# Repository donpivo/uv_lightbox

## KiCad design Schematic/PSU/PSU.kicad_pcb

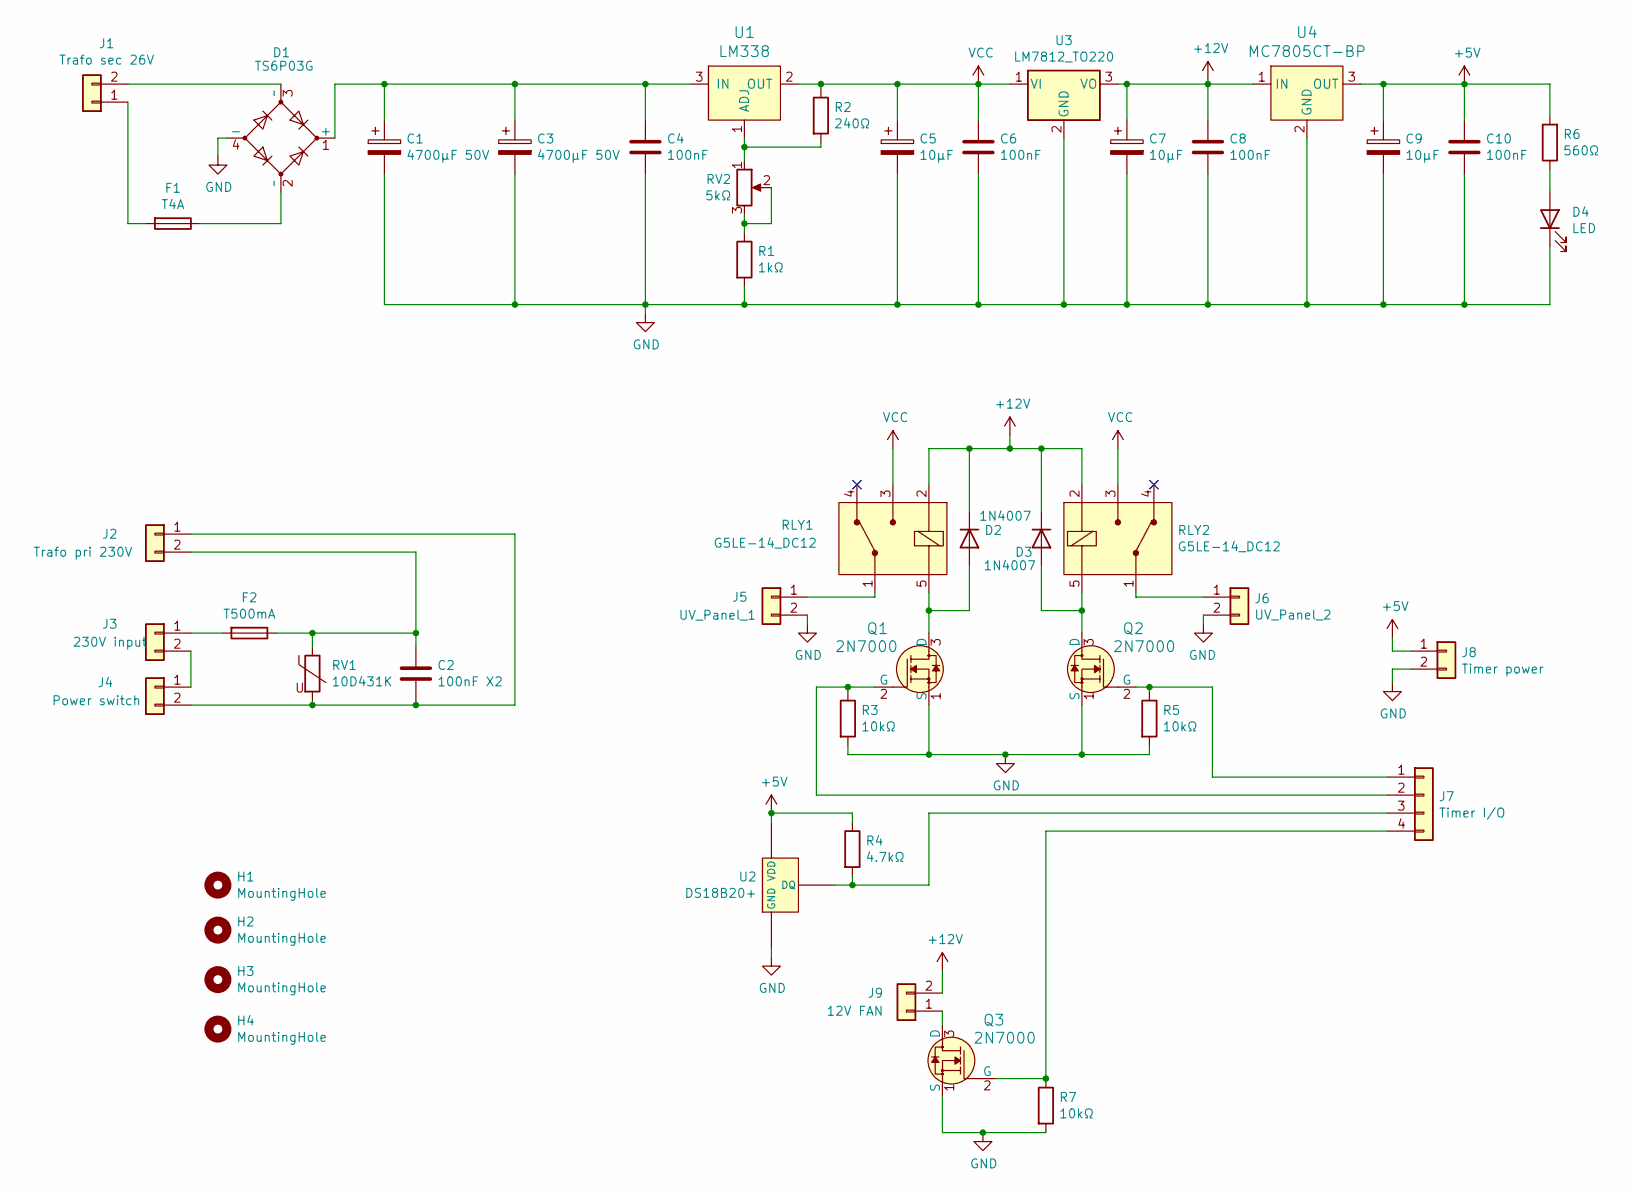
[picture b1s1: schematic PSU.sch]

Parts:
C1, C3: 4700µF 50V; CP_Radial_D22.0mm_P10.00mm_SnapIn
C2: 100nF X2; C_Rect_L18.0mm_W6.0mm_P15.00mm_FKS3_FKP3
C4, C6, C8, C10: 100nF; C_Rect_L7.2mm_W2.5mm_P5.00mm_FKS2_FKP2_MKS2_MKP2
C5, C7, C9: 10µF; CP_Radial_D5.0mm_P2.00mm
D1: TS6P03G; Generic_rectifier
D2, D3: 1N4007; D_DO-41_SOD81_P10.16mm_Horizontal
D4: LED; LED_D3.0mm
F1: T4A; Fuseholder_Cylinder-5x20mm_Closed
F2: T500mA; Fuseholder_Cylinder-5x20mm_Closed
H1, H2, H3, H4: MountingHole; MountingHole_3.2mm_M3
J1: Trafo sec 26V; TerminalBlock_LCSC_P5.08mm
J2: Trafo pri 230V; TerminalBlock_LCSC_P5.08mm
J3: 230V input; TerminalBlock_LCSC_P5.08mm
J4: Power switch; TerminalBlock_LCSC_P5.08mm
J5: UV_Panel_1; TerminalBlock_LCSC_P5.08mm
J6: UV_Panel_2; TerminalBlock_LCSC_P5.08mm
J7: Timer I/O; KF2510-4P
J8: Timer power; KF2510-2P
J9: 12V FAN; KF2510-2P
Q1, Q2, Q3: 2N7000; TO-92-3; MPN 2N7000; Digi-Key_PN 2N7000FS-ND
R1: 1kΩ; R_Axial_DIN0207_L6.3mm_D2.5mm_P7.62mm_Horizontal
R2: 240Ω; R_Axial_DIN0207_L6.3mm_D2.5mm_P7.62mm_Horizontal
R3, R5, R7: 10kΩ; R_Axial_DIN0207_L6.3mm_D2.5mm_P7.62mm_Horizontal
R4: 4.7kΩ; R_Axial_DIN0207_L6.3mm_D2.5mm_P7.62mm_Horizontal
R6: 560Ω; R_Axial_DIN0207_L6.3mm_D2.5mm_P7.62mm_Horizontal
RLY1, RLY2: G5LE-14_DC12; Relay_THT_G5LE-14; MPN G5LE-14 DC12; Digi-Key_PN Z1012-ND
RV1: 10D431K; RV_Disc_D12mm_W4.5mm_P7.5mm
RV2: 5kΩ; Potentiometer_Bourns_3296W_Vertical
U1: LM338; TO-220-3; MPN LM317T; Digi-Key_PN 497-1575-5-ND
U2: DS18B20+; TO127P482X368X883-3
U3: LM7812_TO220; TO-220-3
U4: MC7805CT-BP; TO-220-3; MPN MC7805CT-BP; Digi-Key_PN MC7805CT-BPMS-ND

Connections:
+5V: C9.1, C10.1, J8.1, R4.1, R6.2, U2.3 (VDD), U4.3 (OUT)
+12V: C7.1, C8.1, D2.1 (K), D3.1 (K), J9.2, RLY1.2 (COIL), RLY2.2 (COIL), U3.3 (VO), U4.1 (IN)
GND: C1.2, C3.2, C4.2, C5.2, C6.2, C7.2, C8.2, C9.2, C10.2, D1.4 (-), D4.1 (K), J5.2, J6.2, J8.2, Q1.1 (S), Q2.1 (S), Q3.1 (S), R1.2, R3.2, R5.2, R7.2, U2.1 (GND), U3.2 (GND), U4.2 (GND)
unnamed: C1.1, C3.1, C4.1, D1.1 (+), U1.3 (IN)
unnamed: C2.1, F2.1, J2.2, RV1.1
unnamed: C2.2, J2.1, J4.2, RV1.2
unnamed: D1.2 (~~), F1.1
unnamed: D1.3 (~~), J1.2
unnamed: D2.2 (A), Q1.3 (D), RLY1.5 (COIL)
unnamed: D3.2 (A), Q2.3 (D), RLY2.5 (COIL)
unnamed: D4.2 (A), R6.1
unnamed: F1.2, J1.1
unnamed: F2.2, J3.1
unnamed: J3.2, J4.1
unnamed: J5.1, RLY1.1 (COM)
unnamed: J6.1, RLY2.1 (COM)
unnamed: J7.1, Q2.2 (G), R5.1
unnamed: J7.2, Q1.2 (G), R3.1
unnamed: J7.3, R4.2, U2.2 (DQ)
unnamed: J7.4, Q3.2 (G), R7.1
unnamed: J9.1, Q3.3 (D)
unnamed: R1.1, RV2.2, RV2.3
unnamed: R2.2, RV2.1, U1.1 (ADJ)
VCC: C5.1, C6.1, R2.1, RLY1.3 (NO), RLY2.3 (NO), U1.2 (OUT), U3.1 (VI)

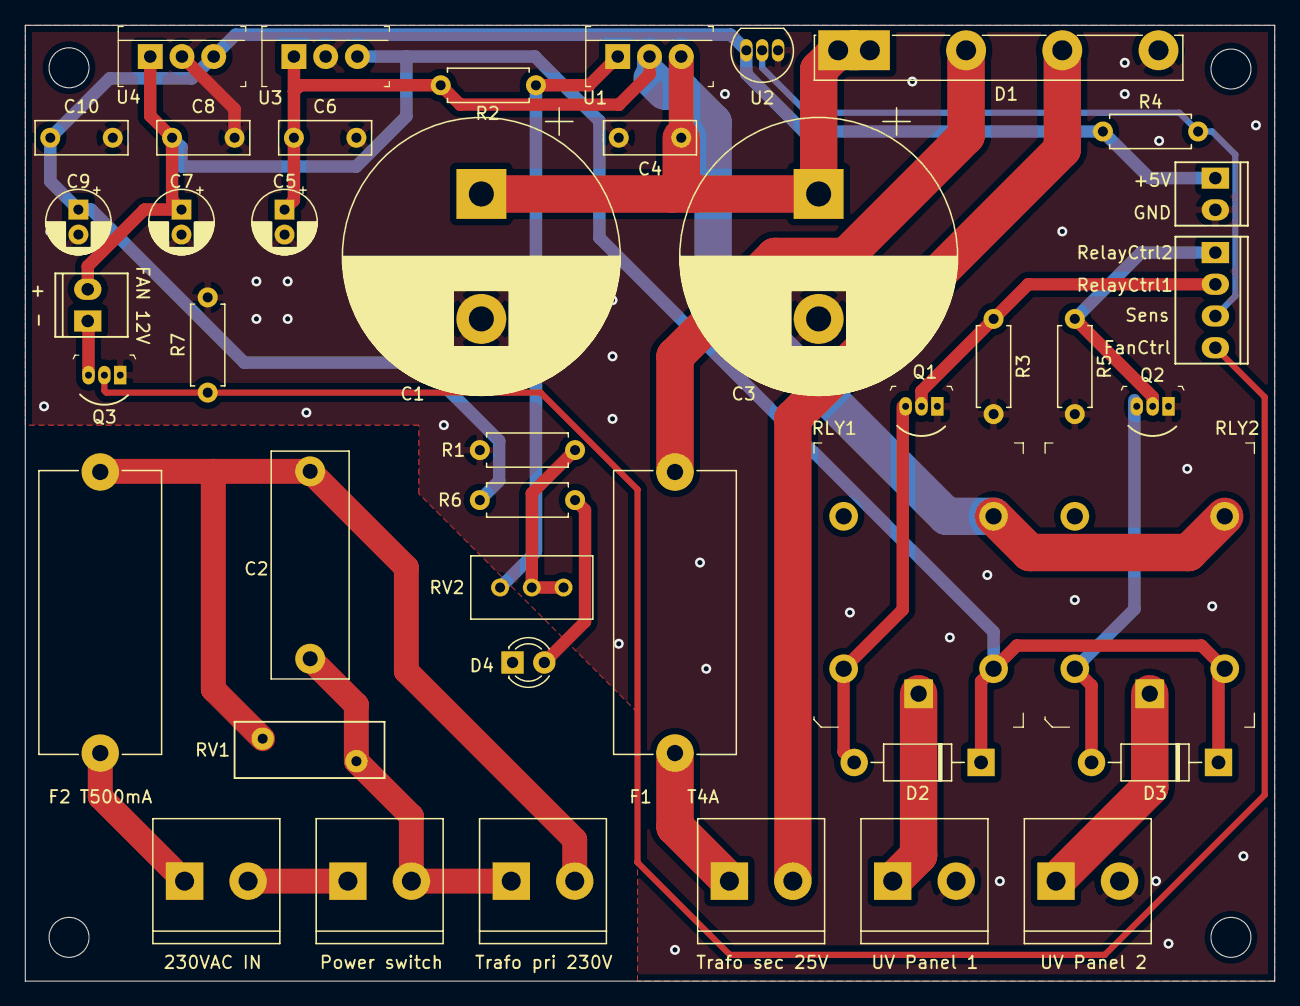
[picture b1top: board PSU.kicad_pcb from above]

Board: 2 copper layers, 100.0 x 76.5 mm, 47 parts (0 on the bottom side), 24 nets.

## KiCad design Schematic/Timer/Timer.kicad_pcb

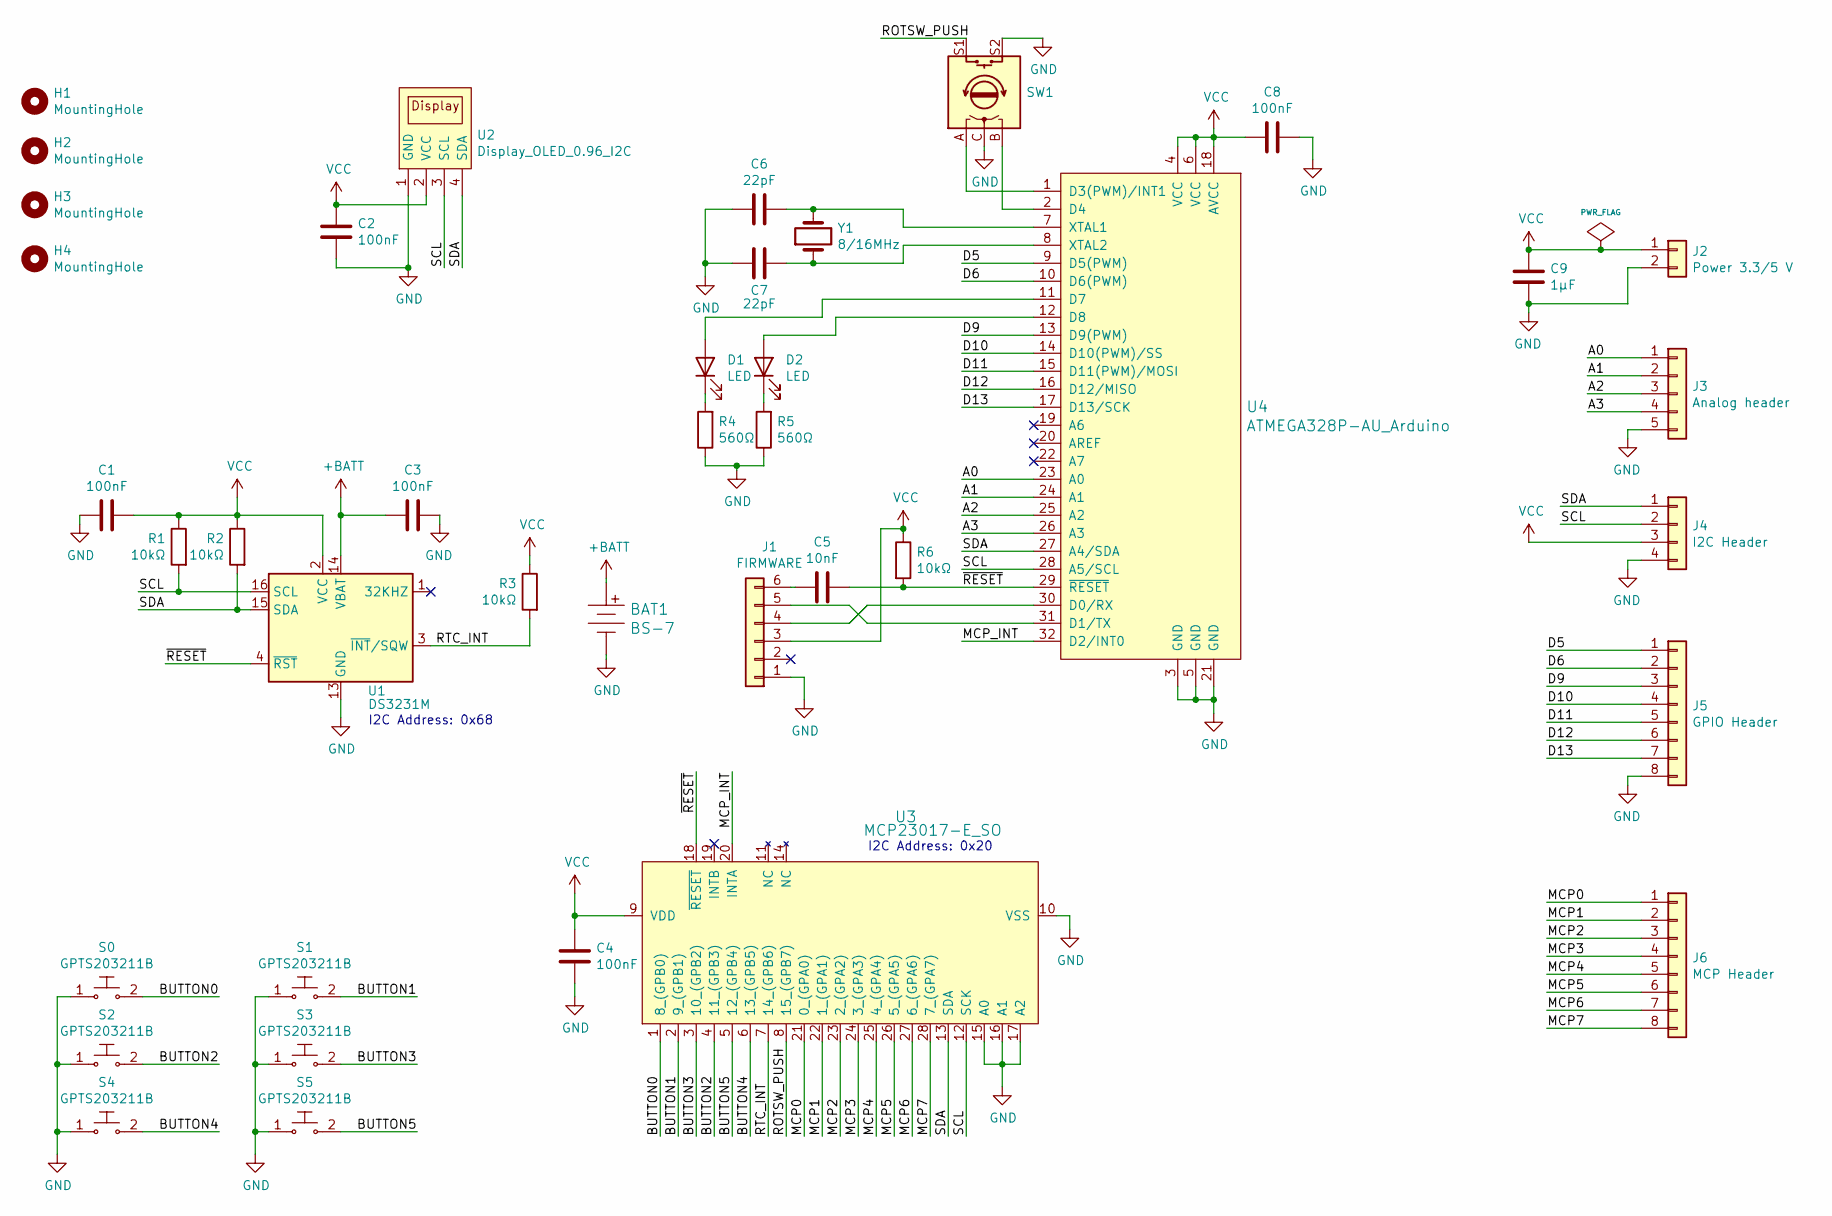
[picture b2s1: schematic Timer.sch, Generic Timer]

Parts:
BAT1: BS-7; Battery_Holder_Coin_2032_BS-7; MPN BS-7; Digi-Key_PN BS-7-ND
C1, C2, C3, C4, C8: 100nF; C_0805_2012Metric_Pad1.15x1.40mm_HandSolder
C5: 10nF; C_0805_2012Metric_Pad1.15x1.40mm_HandSolder
C6, C7: 22pF; C_0805_2012Metric_Pad1.15x1.40mm_HandSolder
C9: 1µF; C_0805_2012Metric_Pad1.15x1.40mm_HandSolder
D1, D2: LED; LED_0805_2012Metric_Pad1.15x1.40mm_HandSolder
H1, H2, H3, H4: MountingHole; MountingHole_3.2mm_M3
J1: FIRMWARE; PinHeader_1x06_P2.54mm_Vertical
J2: Power 3.3/5 V; KF2510-2P
J3: Analog header; KF2510-5P
J4: I2C Header; KF2510-4P
J5: GPIO Header; KF2510-8P
J6: MCP Header; KF2510-8P
R1, R2, R3, R6: 10kΩ; R_0805_2012Metric_Pad1.15x1.40mm_HandSolder
R4, R5: 560Ω; R_0805_2012Metric_Pad1.15x1.40mm_HandSolder
S0, S1, S2, S3, S4, S5: GPTS203211B; SW_PUSH_6mm_H7.3mm; MPN GPTS203211B; Digi-Key_PN CW181-ND
SW1: Rotary_Encoder_Switch; RotaryEncoder_Alps_EC11E-Switch_Vertical_H20mm
U1: DS3231M; SOIC-16W_7.5x10.3mm_P1.27mm
U2: Display_OLED_0.96_I2C; Display_OLED_0.96in_I2C
U3: MCP23017-E_SO; SOIC-28_W7.5mm
U4: ATMEGA328P-AU_Arduino; TQFP-32_7x7mm
Y1: 8/16MHz; Crystal_SMD_HC49-SD

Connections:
+BATT: BAT1.Pos, C3.1, U1.14 (VBAT)
/A0: J3.1, U4.23 (A0)
/A1: J3.2, U4.24 (A1)
/A2: J3.3, U4.25 (A2)
/A3: J3.4, U4.26 (A3)
/BUTTON0: S0.2, U3.1 (8_(GPB0))
/BUTTON1: S1.2, U3.2 (9_(GPB1))
/BUTTON2: S2.2, U3.4 (11_(GPB3))
/BUTTON3: S3.2, U3.3 (10_(GPB2))
/BUTTON4: S4.2, U3.6 (13_(GPB5))
/BUTTON5: S5.2, U3.5 (12_(GPB4))
/D5: J5.1, U4.9 (D5(PWM))
/D6: J5.2, U4.10 (D6(PWM))
/D9: J5.3, U4.13 (D9(PWM))
/D10: J5.4, U4.14 (D10(PWM)/SS)
/D11: J5.5, U4.15 (D11(PWM)/MOSI)
/D12: J5.6, U4.16 (D12/MISO)
/D13: J5.7, U4.17 (D13/SCK)
/MCP0: J6.1, U3.21 (0_(GPA0))
/MCP1: J6.2, U3.22 (1_(GPA1))
/MCP2: J6.3, U3.23 (2_(GPA2))
/MCP3: J6.4, U3.24 (3_(GPA3))
/MCP4: J6.5, U3.25 (4_(GPA4))
/MCP5: J6.6, U3.26 (5_(GPA5))
/MCP6: J6.7, U3.27 (6_(GPA6))
/MCP7: J6.8, U3.28 (7_(GPA7))
/MCP_INT: U3.20 (INTA), U4.32 (D2/INT0)
/ROTSW_PUSH: SW1.S1, U3.8 (15_(GPB7))
/RTC_INT: R3.2, U1.3 (~INT~/SQW), U3.7 (14_(GPB6))
/SCL: J4.2, R1.2, U1.16 (SCL), U2.3 (SCL), U3.12 (SCK), U4.28 (A5/SCL)
/SDA: J4.1, R2.2, U1.15 (SDA), U2.4 (SDA), U3.13 (SDA), U4.27 (A4/SDA)
/~RESET: C5.2, R6.2, U1.4 (~RST), U3.18 (~RESET), U4.29 (~RESET~)
GND: BAT1.Neg, C1.2, C2.1, C3.2, C4.1, C6.1, C7.1, C8.1, C9.1, J1.1, J2.2, J3.5, J4.4, J5.8, R4.1, R5.1, S0.1, S1.1, S2.1, S3.1, S4.1, S5.1, SW1.C, SW1.S2, U1.5 (GND), U1.6 (GND), U1.7 (GND), U1.8 (GND), U1.9 (GND), U1.10 (GND), U1.11 (GND), U1.12 (GND), U1.13 (GND), U2.1 (GND), U3.10 (VSS), U3.15 (A0), U3.16 (A1), U3.17 (A2), U4.3 (GND), U4.5 (GND), U4.21 (GND)
unnamed: C5.1, J1.6
unnamed: C6.2, U4.7 (XTAL1), Y1.2
unnamed: C7.2, U4.8 (XTAL2), Y1.1
unnamed: D1.1 (K), R4.2
unnamed: D1.2 (A), U4.11 (D7)
unnamed: D2.1 (K), R5.2
unnamed: D2.2 (A), U4.12 (D8)
unnamed: J1.4, U4.30 (D0/RX)
unnamed: J1.5, U4.31 (D1/TX)
unnamed: SW1.A, U4.1 (D3(PWM)/INT1)
unnamed: SW1.B, U4.2 (D4)
VCC: C1.1, C2.2, C4.2, C8.2, C9.2, J1.3, J2.1, J4.3, R1.1, R2.1, R3.1, R6.1, U1.2 (VCC), U2.2 (VCC), U3.9 (VDD), U4.4 (VCC), U4.6 (VCC), U4.18 (AVCC)

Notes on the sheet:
I2C Address: 0x68
I2C Address: 0x20

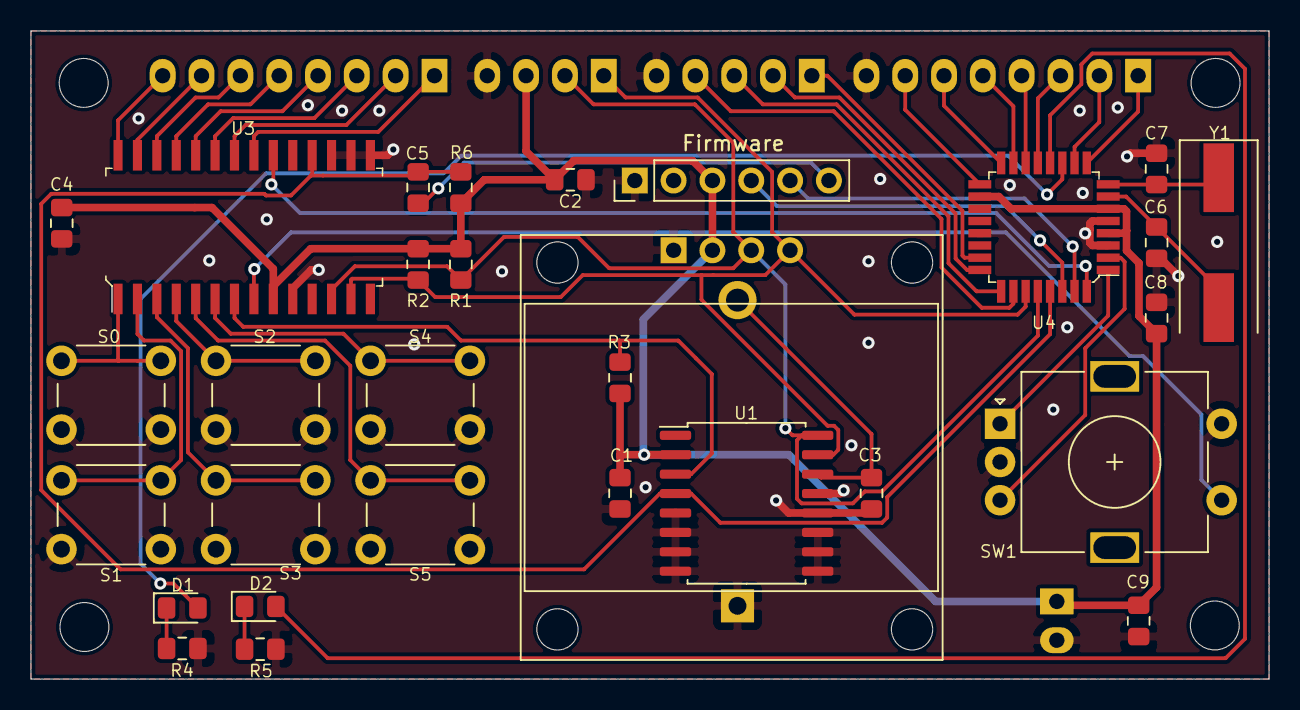
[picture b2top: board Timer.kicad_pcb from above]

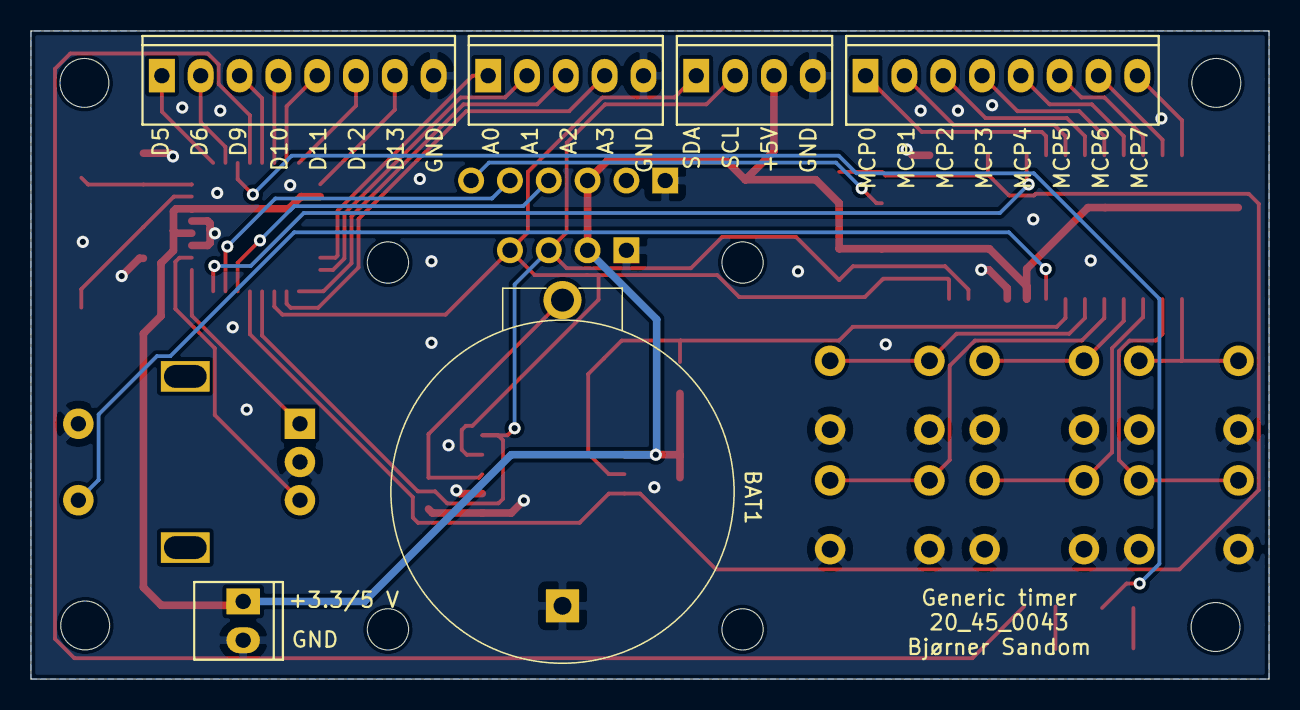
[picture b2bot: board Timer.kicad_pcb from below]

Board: 2 copper layers, 81.0 x 42.4 mm, 40 parts (6 on the bottom side), 45 nets.

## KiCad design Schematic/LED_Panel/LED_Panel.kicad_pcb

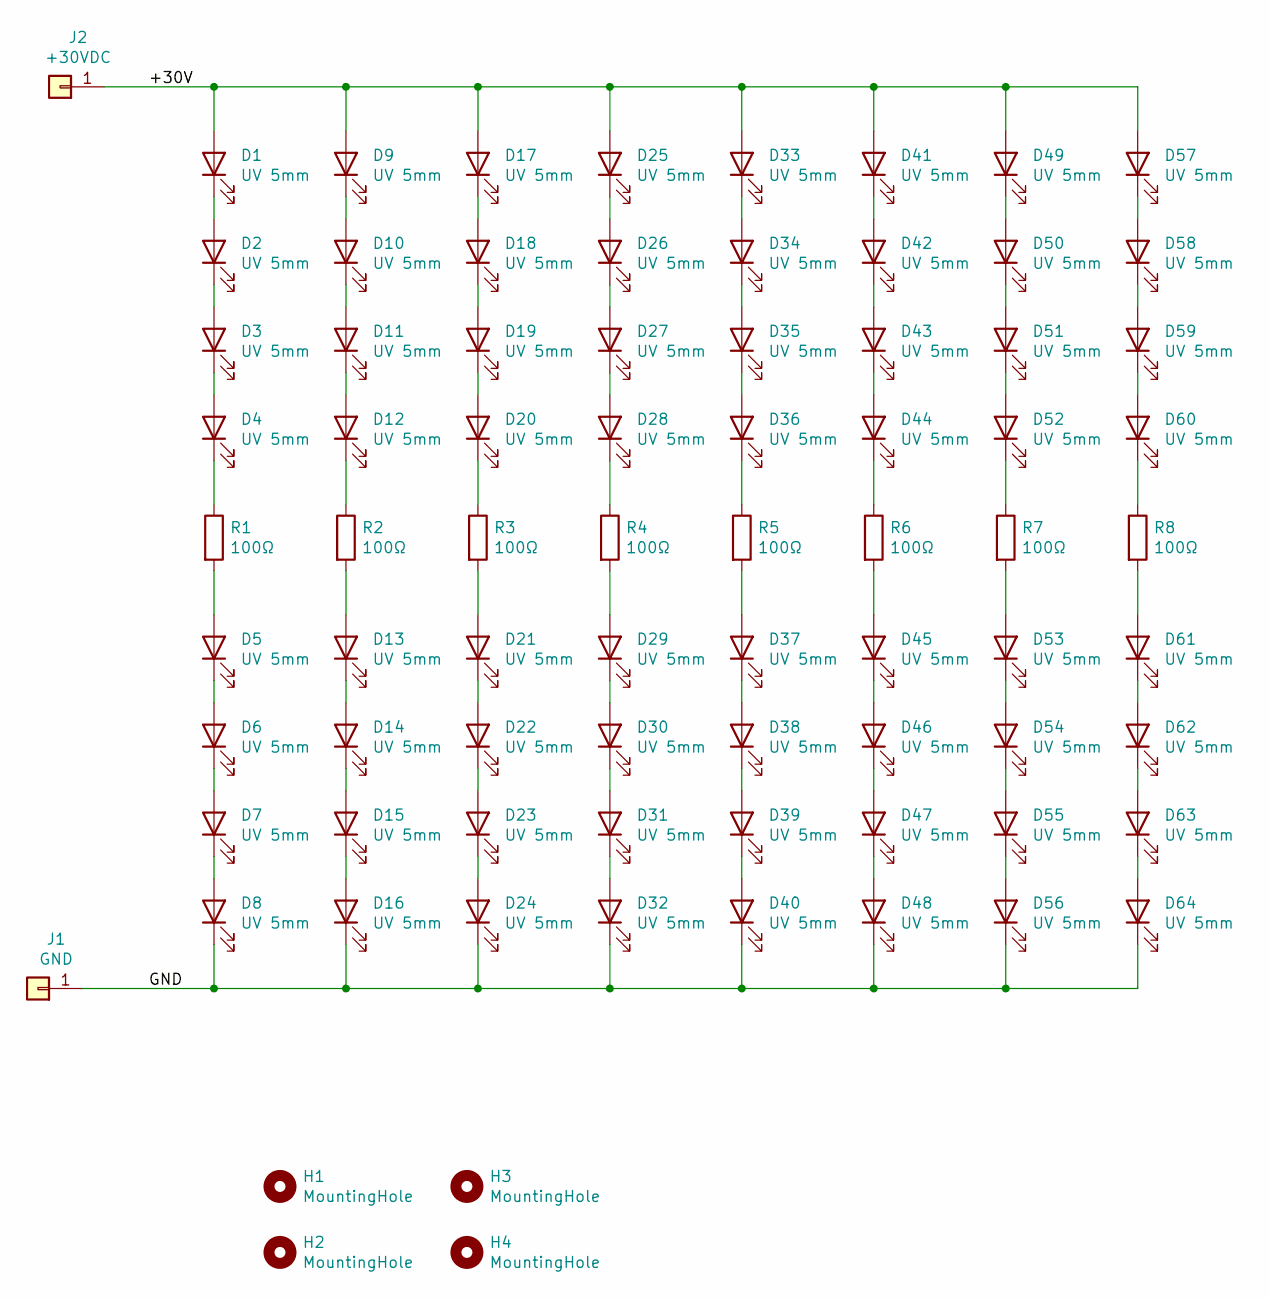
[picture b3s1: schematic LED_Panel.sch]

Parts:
D1, D2, D3, D4, D5, D6, D7, D8, D9, D10, D11, D12, D13, D14, D15, D16, D17, D18, D19, D20, D21, D22, D23, D24, D25, D26, D27, D28, D29, D30, D31, D32, D33, D34, D35, D36, D37, D38, D39, D40, D41, D42, D43, D44, D45, D46, D47, D48, D49, D50, D51, D52, D53, D54, D55, D56, D57, D58, D59, D60, D61, D62, D63, D64: UV 5mm; LED_D5.0mm_Clear
H1, H2, H3, H4: MountingHole; MountingHole_3.2mm_M3
J1: GND; TestPoint_Loop_D3.80mm_Drill2.0mm
J2: +30VDC; TestPoint_Loop_D3.80mm_Drill2.0mm
R1, R2, R3, R4, R5, R6, R7, R8: 100Ω; R_Axial_DIN0207_L6.3mm_D2.5mm_P7.62mm_Horizontal

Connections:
/+30V: D1.2 (A), D9.2 (A), D17.2 (A), D25.2 (A), D33.2 (A), D41.2 (A), D49.2 (A), D57.2 (A), J2.1
/GND: D8.1 (K), D16.1 (K), D24.1 (K), D32.1 (K), D40.1 (K), D48.1 (K), D56.1 (K), D64.1 (K), J1.1
unnamed: D1.1 (K), D2.2 (A)
unnamed: D2.1 (K), D3.2 (A)
unnamed: D3.1 (K), D4.2 (A)
unnamed: D4.1 (K), R1.1
unnamed: D5.1 (K), D6.2 (A)
unnamed: D5.2 (A), R1.2
unnamed: D6.1 (K), D7.2 (A)
unnamed: D7.1 (K), D8.2 (A)
unnamed: D10.1 (K), D11.2 (A)
unnamed: D9.1 (K), D10.2 (A)
unnamed: D11.1 (K), D12.2 (A)
unnamed: D12.1 (K), R2.1
unnamed: D13.1 (K), D14.2 (A)
unnamed: D13.2 (A), R2.2
unnamed: D14.1 (K), D15.2 (A)
unnamed: D15.1 (K), D16.2 (A)
unnamed: D17.1 (K), D18.2 (A)
unnamed: D18.1 (K), D19.2 (A)
unnamed: D19.1 (K), D20.2 (A)
unnamed: D20.1 (K), R3.1
unnamed: D21.1 (K), D22.2 (A)
unnamed: D21.2 (A), R3.2
unnamed: D22.1 (K), D23.2 (A)
unnamed: D23.1 (K), D24.2 (A)
unnamed: D25.1 (K), D26.2 (A)
unnamed: D26.1 (K), D27.2 (A)
unnamed: D27.1 (K), D28.2 (A)
unnamed: D28.1 (K), R4.1
unnamed: D29.1 (K), D30.2 (A)
unnamed: D29.2 (A), R4.2
unnamed: D30.1 (K), D31.2 (A)
unnamed: D31.1 (K), D32.2 (A)
unnamed: D33.1 (K), D34.2 (A)
unnamed: D34.1 (K), D35.2 (A)
unnamed: D35.1 (K), D36.2 (A)
unnamed: D36.1 (K), R5.1
unnamed: D37.1 (K), D38.2 (A)
unnamed: D37.2 (A), R5.2
unnamed: D38.1 (K), D39.2 (A)
unnamed: D39.1 (K), D40.2 (A)
unnamed: D41.1 (K), D42.2 (A)
unnamed: D42.1 (K), D43.2 (A)
unnamed: D43.1 (K), D44.2 (A)
unnamed: D44.1 (K), R6.1
unnamed: D45.1 (K), D46.2 (A)
unnamed: D45.2 (A), R6.2
unnamed: D46.1 (K), D47.2 (A)
unnamed: D47.1 (K), D48.2 (A)
unnamed: D49.1 (K), D50.2 (A)
unnamed: D50.1 (K), D51.2 (A)
unnamed: D51.1 (K), D52.2 (A)
unnamed: D52.1 (K), R7.1
unnamed: D53.1 (K), D54.2 (A)
unnamed: D53.2 (A), R7.2
unnamed: D54.1 (K), D55.2 (A)
unnamed: D55.1 (K), D56.2 (A)
unnamed: D57.1 (K), D58.2 (A)
unnamed: D58.1 (K), D59.2 (A)
unnamed: D59.1 (K), D60.2 (A)
unnamed: D60.1 (K), R8.1
unnamed: D61.1 (K), D62.2 (A)
unnamed: D61.2 (A), R8.2
unnamed: D62.1 (K), D63.2 (A)
unnamed: D63.1 (K), D64.2 (A)

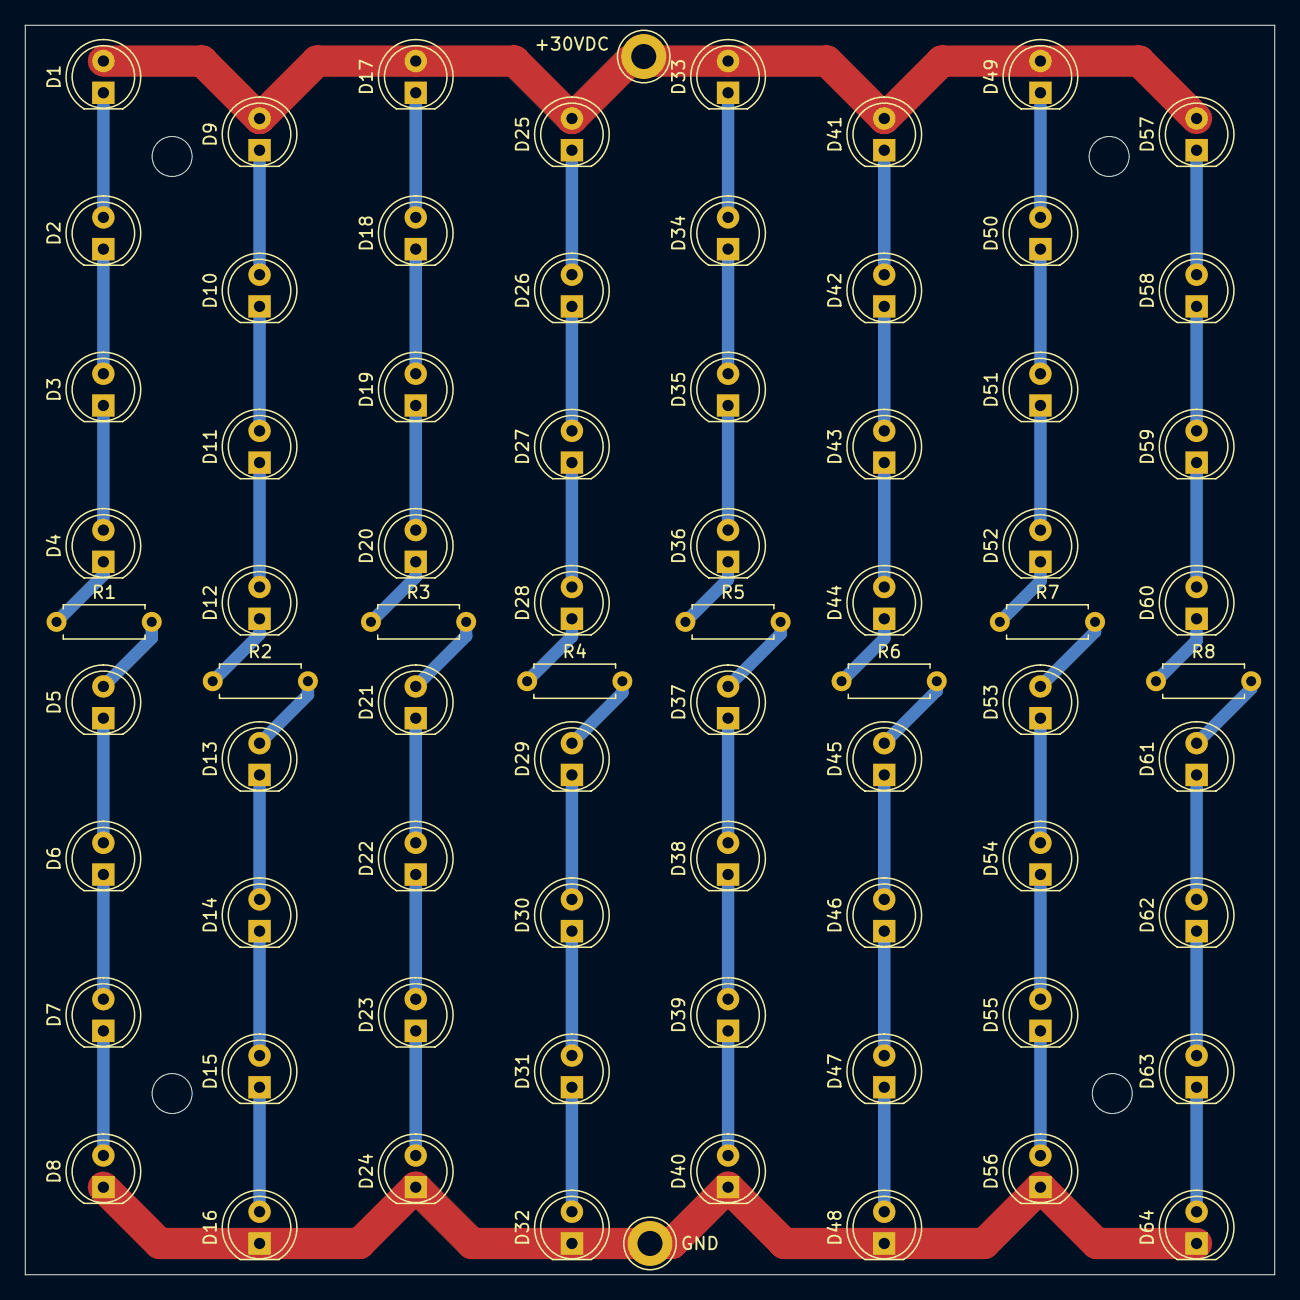
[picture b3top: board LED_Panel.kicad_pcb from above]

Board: 2 copper layers, 100.0 x 100.0 mm, 78 parts (0 on the bottom side), 66 nets.

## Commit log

2020-11-03 Early version with DS3231M RTC
2020-11-03 New timer with the more precise DS3231 + more digital I/O ports exposed.
2020-11-03 PSU board: Added temperature sensor and fan driver. 12V relays.
2020-11-04 PSU: corrected silkscreen for timer inputs
2020-12-04 Code for hardware test
